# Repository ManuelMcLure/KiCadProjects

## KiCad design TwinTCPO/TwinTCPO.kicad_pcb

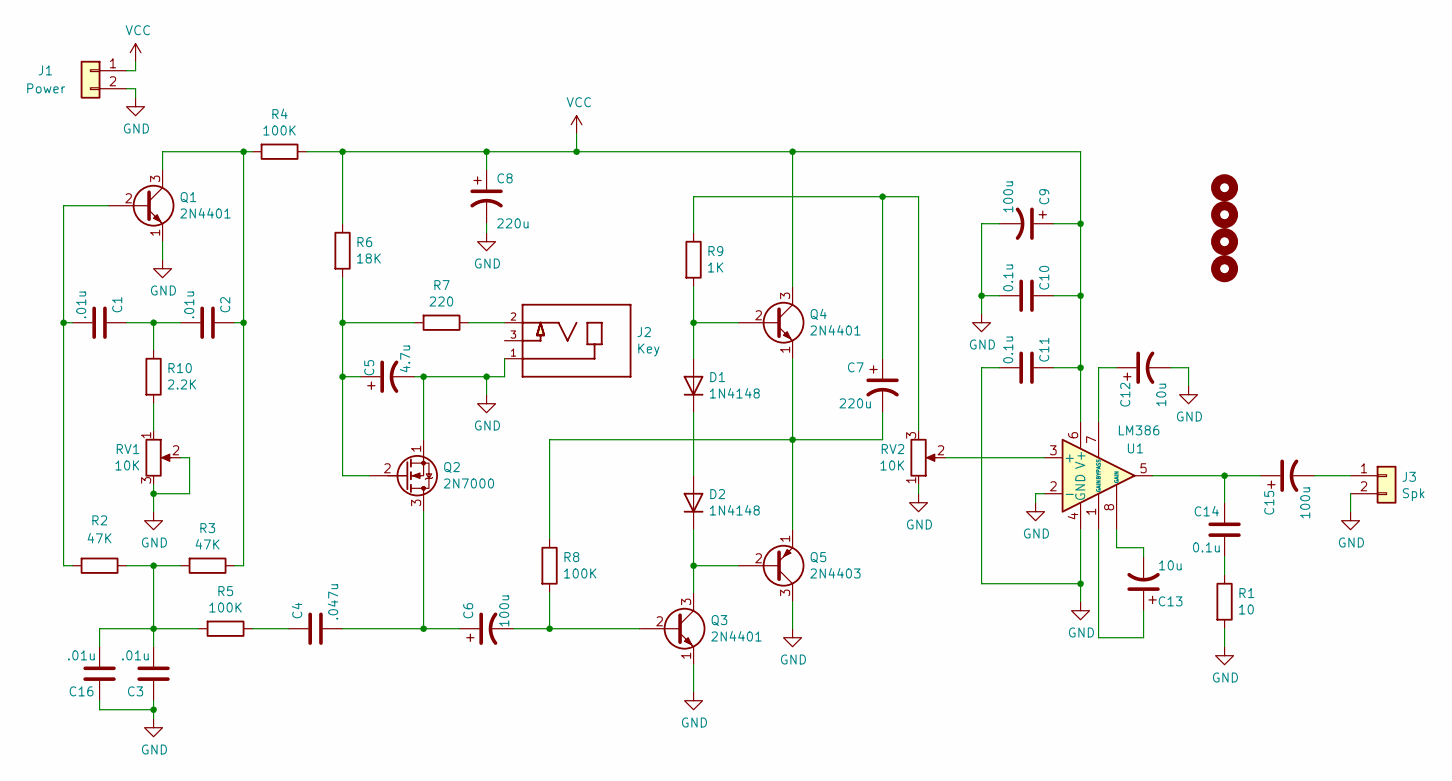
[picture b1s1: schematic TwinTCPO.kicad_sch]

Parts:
C1, C2, C3, C16: .01u; C_Disc_D4.7mm_W2.5mm_P5.00mm
C4: .047u; C_Disc_D4.7mm_W2.5mm_P5.00mm
C5: 4.7u; CP_Radial_D5.0mm_P2.50mm
C6, C9, C15: 100u; CP_Radial_D5.0mm_P2.00mm
C7, C8: 220u; CP_Radial_D6.3mm_P2.50mm
C10, C11, C14: 0.1u; C_Disc_D4.7mm_W2.5mm_P5.00mm
C12, C13: 10u; CP_Radial_D5.0mm_P2.50mm
D1, D2: 1N4148; D_DO-35_SOD27_P7.62mm_Horizontal
H1, H2, H3, H4: MountingHole; MountingHole_3.2mm_M3_DIN965
J1: Power; Molex_KK-254_AE-6410-02A_1x02_P2.54mm_Vertical
J2: Key; CUI_MJ-3536N; PART_REV B
J3: Spk; Molex_KK-254_AE-6410-02A_1x02_P2.54mm_Vertical
Q1, Q3, Q4: 2N4401; TO-92L_Inline_Wide
Q2: 2N7000; TO-92L_Inline_Wide
Q5: 2N4403; TO-92L_Inline_Wide
R1: 10; R_Axial_DIN0207_L6.3mm_D2.5mm_P2.54mm_Vertical
R2, R3: 47K; R_Axial_DIN0207_L6.3mm_D2.5mm_P2.54mm_Vertical
R4, R5, R8: 100K; R_Axial_DIN0207_L6.3mm_D2.5mm_P2.54mm_Vertical
R6: 18K; R_Axial_DIN0207_L6.3mm_D2.5mm_P2.54mm_Vertical
R7: 220; R_Axial_DIN0207_L6.3mm_D2.5mm_P2.54mm_Vertical
R9: 1K; R_Axial_DIN0207_L6.3mm_D2.5mm_P2.54mm_Vertical
R10: 2.2K; R_Axial_DIN0207_L6.3mm_D2.5mm_P2.54mm_Vertical
RV1, RV2: 10K; P120PK
U1: LM386; DIP-8_W7.62mm_Socket

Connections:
GND: C3.1, C5.2, C8.2, C9.2, C10.2, C11.2, C12.2, C16.1, J1.2, J2.1, J3.2, Q1.1 (E), Q2.1 (S), Q3.1 (E), Q5.3 (C), R1.2, RV1.2, RV1.3, RV2.1, U1.2 (-), U1.4 (GND)
unnamed: C1.1, C2.2, R10.1
unnamed: C1.2, Q1.2 (B), R2.2
unnamed: C2.1, Q1.3 (C), R3.1, R4.2
unnamed: C4.1, R5.1
unnamed: C4.2, C6.1, Q2.3 (D)
unnamed: C5.1, Q2.2 (G), R6.2, R7.2
unnamed: C6.2, Q3.2 (B), R8.2
unnamed: C7.1, R9.1, RV2.3
unnamed: C7.2, Q4.1 (E), Q5.1 (E), R8.1
unnamed: C12.1, U1.7 (BYPASS)
unnamed: C13.1, U1.1 (GAIN)
unnamed: C13.2, U1.8 (GAIN)
unnamed: C14.1, C15.1, U1.5
unnamed: C14.2, R1.1
unnamed: C15.2, J3.1
unnamed: C3.2, C16.2, R2.1, R3.2, R5.2
unnamed: D1.1 (K), D2.2 (A)
unnamed: D1.2 (A), Q4.2 (B), R9.2
unnamed: D2.1 (K), Q3.3 (C), Q5.2 (B)
unnamed: J2.2, R7.1
unnamed: R10.2, RV1.1
unnamed: RV2.2, U1.3 (+)
VCC: C8.1, C9.1, C10.1, C11.1, J1.1, Q4.3 (C), R4.1, R6.1, U1.6 (V+)

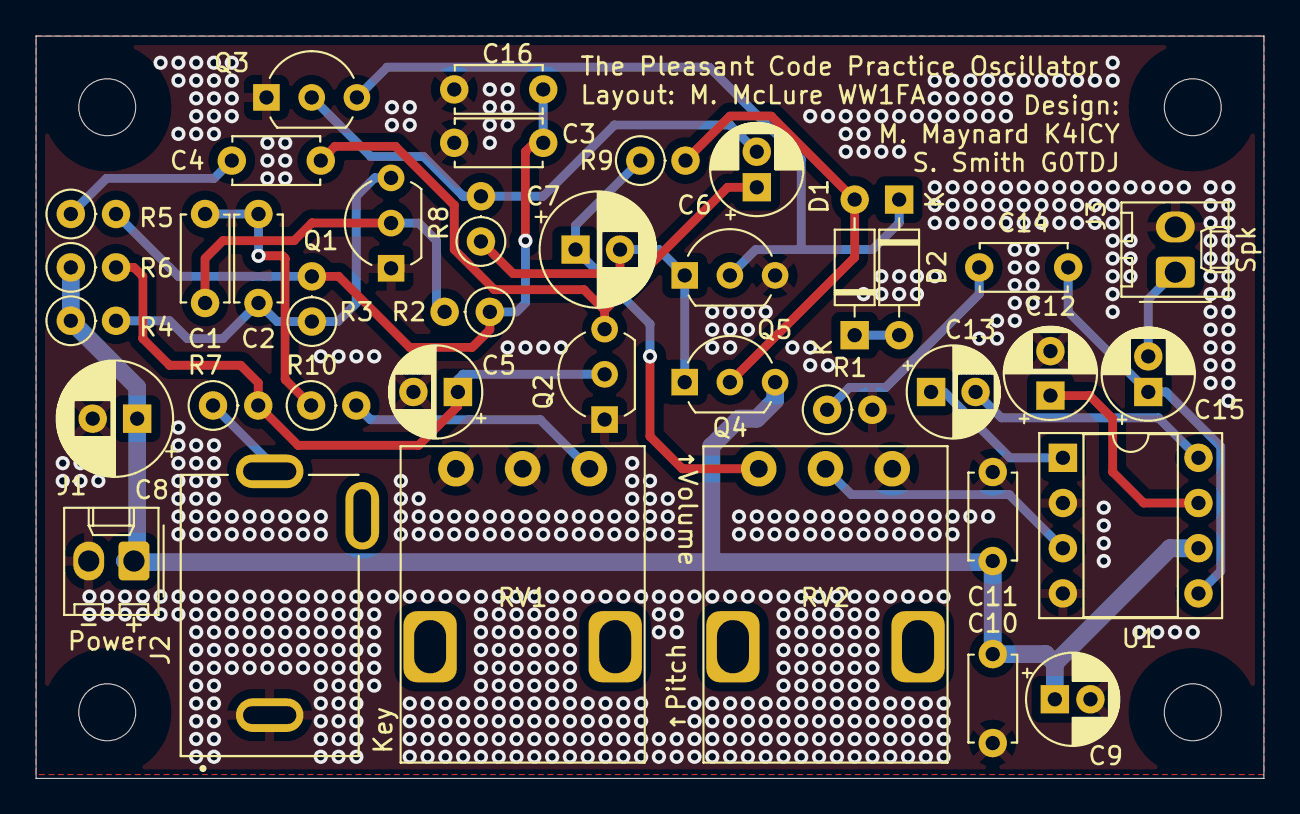
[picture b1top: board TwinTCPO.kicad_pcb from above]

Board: 2 copper layers, 69.0 x 41.7 mm, 43 parts (0 on the bottom side), 24 nets.

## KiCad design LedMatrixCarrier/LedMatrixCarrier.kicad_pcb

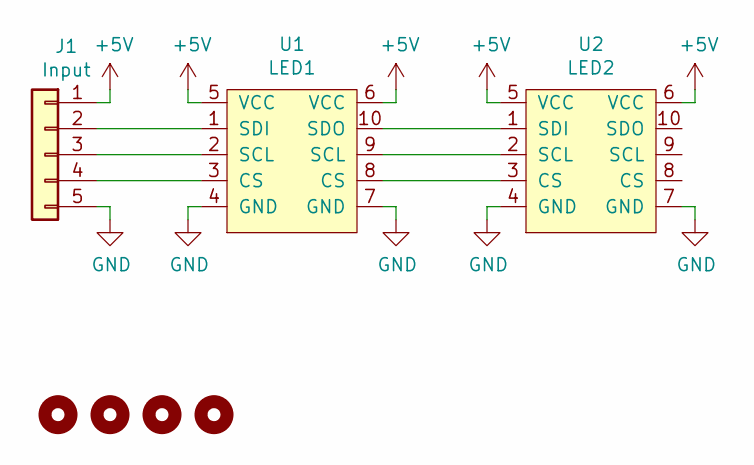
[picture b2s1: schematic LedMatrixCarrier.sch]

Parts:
H1, H2, H3, H4: MountingHole; MountingHole_3.2mm_M3_DIN965
J1: Input; PinHeader_1x05_P2.54mm_Vertical
U1: LED1; RoboDyn_MAX7221_LED_Matrix
U2: LED2; RoboDyn_MAX7221_LED_Matrix

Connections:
+5V: J1.1, U1.5 (VCC), U1.6 (VCC), U2.5 (VCC), U2.6 (VCC)
GND: J1.5, U1.4 (GND), U1.7 (GND), U2.4 (GND), U2.7 (GND)
unnamed: J1.2, U1.1 (SDI)
unnamed: J1.3, U1.2 (SCL)
unnamed: J1.4, U1.3 (CS)
unnamed: U1.8 (CS), U2.3 (CS)
unnamed: U1.9 (SCL), U2.2 (SCL)
unnamed: U1.10 (SDO), U2.1 (SDI)

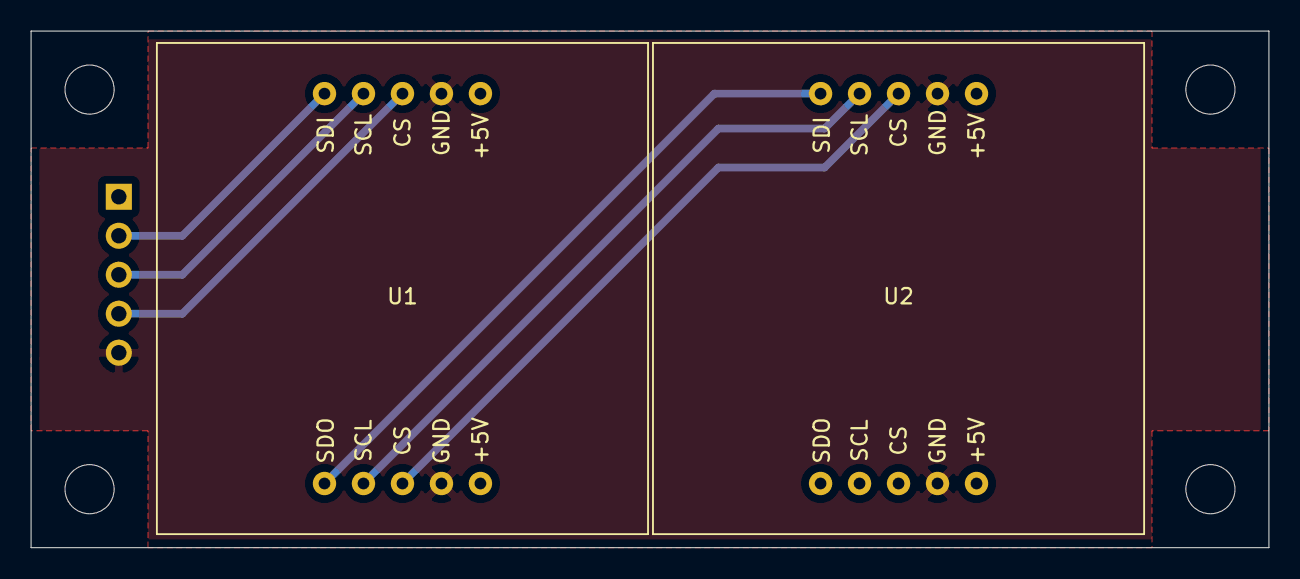
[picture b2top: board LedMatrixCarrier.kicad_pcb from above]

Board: 2 copper layers, 80.6 x 33.7 mm, 7 parts (1 on the bottom side), 8 nets.

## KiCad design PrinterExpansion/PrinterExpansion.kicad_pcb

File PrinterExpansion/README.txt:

This project requires the MyLibrary symbol and footprint libraries in ..\Libraries.

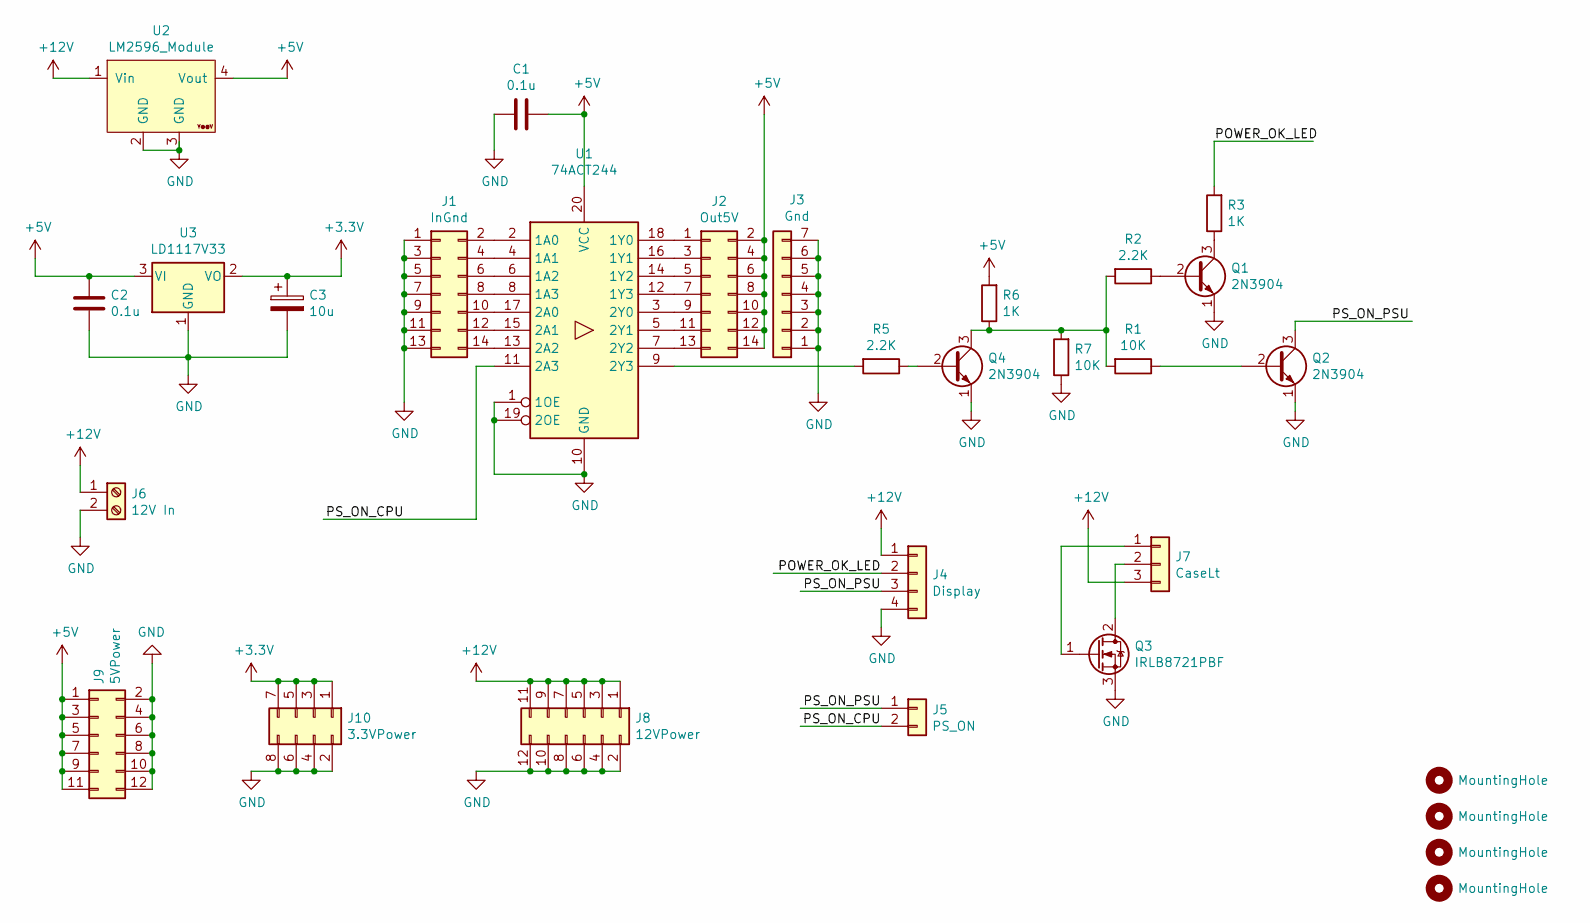
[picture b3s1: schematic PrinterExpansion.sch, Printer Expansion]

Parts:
C1, C2: 0.1u; C_Disc_D4.7mm_W2.5mm_P5.00mm
C3: 10u; CP_Radial_D5.0mm_P2.50mm
H1, H2, H3, H4: MountingHole; MountingHole_3.2mm_M3_ISO7380
J1: InGnd; PinHeader_2x07_P2.54mm_Vertical
J2: Out5V; PinHeader_2x07_P2.54mm_Vertical
J3: Gnd; PinHeader_1x07_P2.54mm_Vertical
J4: Display; Molex_KK-254_AE-6410-04A_1x04_P2.54mm_Vertical
J5: PS_ON; Molex_KK-254_AE-6410-02A_1x02_P2.54mm_Vertical
J6: 12V In; TerminalBlock_Dinkle_EK500_2Pole
J7: CaseLt; Molex_KK-254_AE-6410-03A_1x03_P2.54mm_Vertical
J8: 12VPower; PinHeader_2x06_P2.54mm_Vertical
J9: 5VPower; PinHeader_2x06_P2.54mm_Vertical
J10: 3.3VPower; PinHeader_2x04_P2.54mm_Vertical
Q1, Q2, Q4: 2N3904; TO-92_Inline_Wide
Q3: IRLB8721PBF; TO-220-3_Vertical
R1, R7: 10K; R_Axial_DIN0207_L6.3mm_D2.5mm_P10.16mm_Horizontal
R2, R5: 2.2K; R_Axial_DIN0207_L6.3mm_D2.5mm_P10.16mm_Horizontal
R3, R6: 1K; R_Axial_DIN0207_L6.3mm_D2.5mm_P10.16mm_Horizontal
U1: 74ACT244; DIP-20_W7.62mm_Socket
U2: LM2596_Module; YAAJ_DCDC_StepDown_LM2596
U3: LD1117V33; TO-220-3_Vertical

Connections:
+3V3: C3.1, J10.1, J10.3, J10.5, J10.7, U3.2 (VO)
+5V: C1.1, C2.1, J2.2, J2.4, J2.6, J2.8, J2.10, J2.12, J2.14, J9.1, J9.3, J9.5, J9.7, J9.9, J9.11, R6.2, U1.20 (VCC), U2.4 (Vout), U3.3 (VI)
+12V: J4.1, J6.1, J7.3, J8.1, J8.3, J8.5, J8.7, J8.9, J8.11, U2.1 (Vin)
/POWER_OK_LED: J4.2, R3.2
/PS_ON_CPU: J5.2, U1.11 (2A3)
/PS_ON_PSU: J4.3, J5.1, Q2.3 (C)
GND: C1.2, C2.2, C3.2, J1.1, J1.3, J1.5, J1.7, J1.9, J1.11, J1.13, J3.1, J3.2, J3.3, J3.4, J3.5, J3.6, J3.7, J4.4, J6.2, J8.2, J8.4, J8.6, J8.8, J8.10, J8.12, J9.2, J9.4, J9.6, J9.8, J9.10, J9.12, J10.2, J10.4, J10.6, J10.8, Q1.1 (E), Q2.1 (E), Q3.3 (S), Q4.1 (E), R7.1, U1.1 (1OE), U1.10 (GND), U1.19 (2OE), U2.2 (GND), U2.3 (GND), U3.1 (GND)
unnamed: J1.2, U1.2 (1A0)
unnamed: J1.4, U1.4 (1A1)
unnamed: J1.6, U1.6 (1A2)
unnamed: J1.8, U1.8 (1A3)
unnamed: J1.10, U1.17 (2A0)
unnamed: J1.12, U1.15 (2A1)
unnamed: J1.14, U1.13 (2A2)
unnamed: J2.1, U1.18 (1Y0)
unnamed: J2.3, U1.16 (1Y1)
unnamed: J2.5, U1.14 (1Y2)
unnamed: J2.7, U1.12 (1Y3)
unnamed: J2.9, U1.3 (2Y0)
unnamed: J2.11, U1.5 (2Y1)
unnamed: J2.13, U1.7 (2Y2)
unnamed: J7.1, Q3.1 (G)
unnamed: J7.2, Q3.2 (D)
unnamed: Q1.2 (B), R2.1
unnamed: Q1.3 (C), R3.1
unnamed: Q2.2 (B), R1.1
unnamed: Q4.2 (B), R5.1
unnamed: Q4.3 (C), R1.2, R2.2, R6.1, R7.2
unnamed: R5.2, U1.9 (2Y3)

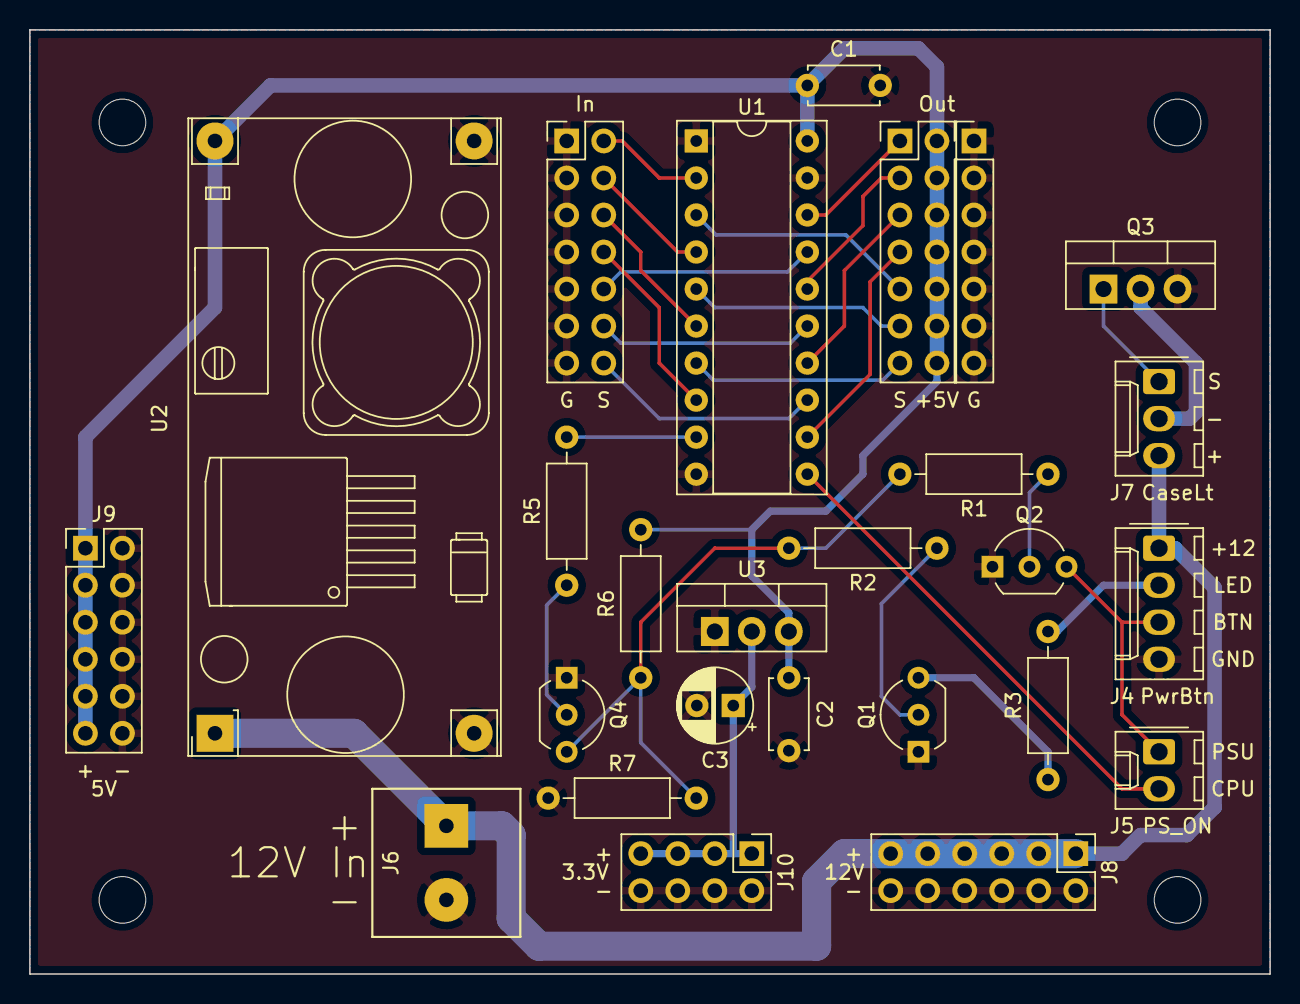
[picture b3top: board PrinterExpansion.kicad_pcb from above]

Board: 2 copper layers, 85.1 x 64.8 mm, 30 parts (0 on the bottom side), 29 nets.

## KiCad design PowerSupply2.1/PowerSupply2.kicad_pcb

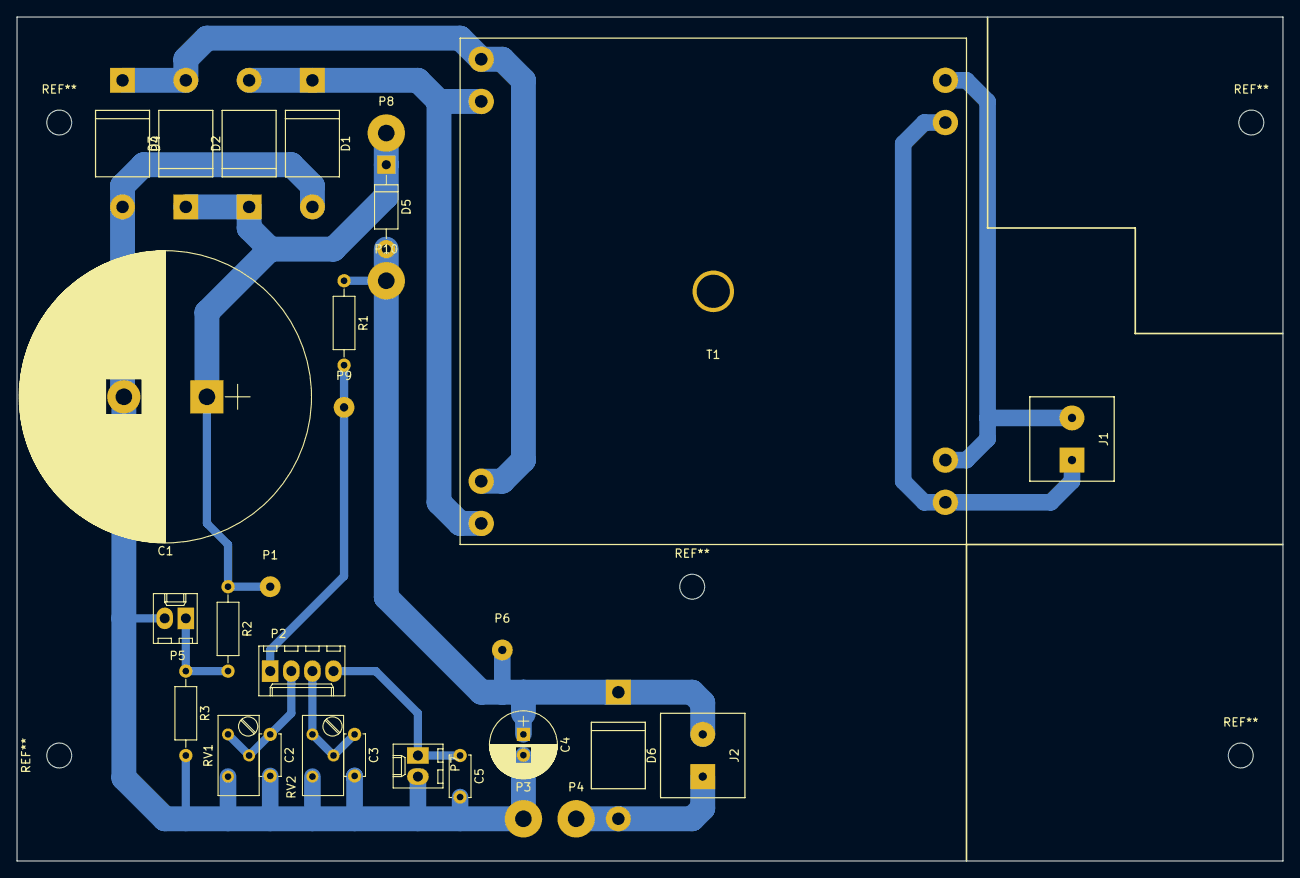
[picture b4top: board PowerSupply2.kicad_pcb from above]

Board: 2 copper layers, 152.4 x 101.6 mm, 29 parts (0 on the bottom side), 13 nets.

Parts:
C1: 27000uF 25V; CP_Radial_D35.0mm_P10.00mm_SnapIn
C2, C3, C5: 10uF; C_Disc_D5.0mm_W2.5mm_P5.00mm
C4: 150uF; CP_Radial_D8.0mm_P2.50mm
D1, D2, D3, D4, D6: RK46
D5: 1N4001; D_DO-41_SOD81_P10.16mm_Horizontal
J1: AC_In; TerminalBlock_Dinkle_EK500_2Pole
J2: VOut; TerminalBlock_Dinkle_EK500_2Pole
P1: DispPwr; SolderWirePad_single_1mmDrill
P2: VSelect; Molex_KK-6410-04_04x2.54mm_Straight
P3: Curr-; SolderWirePad_single_2mmDrill
P4: Curr+; SolderWirePad_single_2mmDrill
P5: PWR_LED; Molex_KK-6410-02_02x2.54mm_Straight
P6: VSense; SolderWirePad_single_1mmDrill
P7: VVar; Molex_KK-6410-02_02x2.54mm_Straight
P8: VRegIn; SolderWirePad_single_2mmDrill
P9: VRegAdj; SolderWirePad_single_1mmDrill
P10: VRegOut; SolderWirePad_single_2mmDrill
R1: 121; R_Axial_DIN0207_L6.3mm_D2.5mm_P10.16mm_Horizontal
R2: 150; R_Axial_DIN0207_L6.3mm_D2.5mm_P10.16mm_Horizontal
R3: 1K; R_Axial_DIN0207_L6.3mm_D2.5mm_P10.16mm_Horizontal
RV1, RV2: 500; Potentiometer_Trimmer_Bourns_3296Y
T1: Talema_70060K

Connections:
/AC7V_1: D1.1, D2.2, T1.11, T1.13
/AC7V_2: D3.2, D4.1, T1.12, T1.14
/ACLive: J1.1, T1.4, T1.6
/ACNeutral: J1.2, T1.3, T1.5
/Gnd: C1.2, C2.2, C3.2, C4.2, C5.2, D1.2, D4.2, P3.1, P5.2, P7.2, R3.2, RV1.3, RV2.3
/Reg+: C4.1, D5.2, D6.1, J2.2, P6.1, P10.1, R1.1
/Unreg+: C1.1, D2.1, D3.1, D5.1, P1.1, P8.1, R2.1
unnamed: C2.1, P2.2, RV1.1, RV1.2
unnamed: C3.1, P2.3, RV2.1, RV2.2
unnamed: C5.1, P2.4, P7.1
unnamed: D6.2, J2.1, P4.1
unnamed: P2.1, P9.1, R1.2
unnamed: P5.1, R2.2, R3.1

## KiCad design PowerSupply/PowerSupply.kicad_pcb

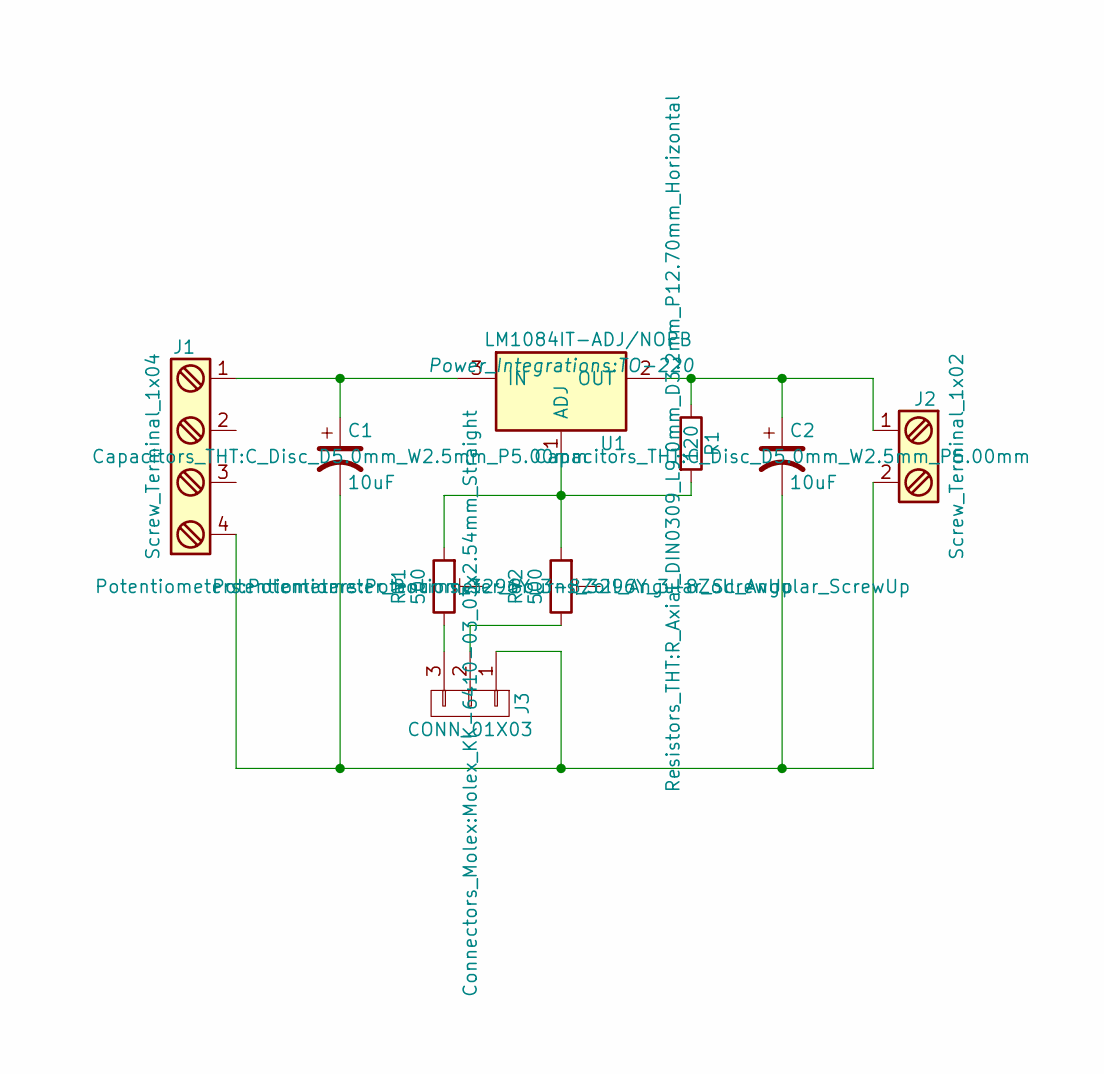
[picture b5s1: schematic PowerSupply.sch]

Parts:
C1, C2: 10uF; C_Disc_D5.0mm_W2.5mm_P5.00mm
J1: Screw_Terminal_1x04; TerminalBlock_Pheonix_MKDS1.5-4pol
J2: Screw_Terminal_1x02; TerminalBlock_Pheonix_MKDS1.5-2pol
J3: CONN_01X03; Molex_KK-6410-03_03x2.54mm_Straight
R1: 120; R_Axial_DIN0309_L9.0mm_D3.2mm_P12.70mm_Horizontal
RV1, RV2: 500; Potentiometer_Bourns_3296Y_3-8Zoll_Angular_ScrewUp
U1: LM1084IT-ADJ/NOPB; TO-220

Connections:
unnamed: C1.1, J1.1, U1.3 (IN)
unnamed: C1.2, C2.2, J1.4, J2.2, J3.1
unnamed: C2.1, J2.1, R1.1, U1.2 (OUT)
unnamed: J3.2, RV2.3
unnamed: J3.3, RV1.3
unnamed: R1.2, RV1.1, RV2.1, U1.1 (ADJ)

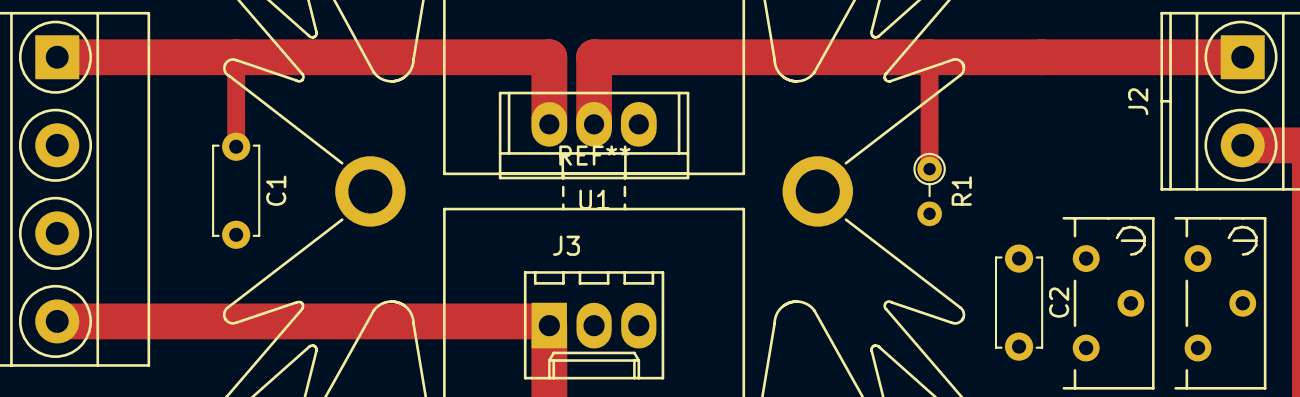
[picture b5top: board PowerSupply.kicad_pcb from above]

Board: 2 copper layers, 9 parts (0 on the bottom side), 6 nets.

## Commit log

2021-09-18 Initial checkin
2021-09-18 Change license and add text to PCB.
2021-09-18 Use actual copyright symbol
2021-09-18 Fix buck module 3D view.
2021-09-19 Fix library references
2021-09-20 Fix library references (again)
2021-10-10 Fix origin
2021-10-13 Add RoboDyn MAX7221 LED Matrix
2021-10-13 Check in LED Matrix carrier
2021-10-14 Add Gerbers to ignored files
2021-10-17 First checking TwinTCPO
2021-10-22 P129PK pot footprint
2021-10-23 Add new components
2021-10-23 Ready for production
2021-10-23 Fix for Kicad 5.99/6.x
2021-10-23 Bring up to Kicad 5.99/6.x
2021-10-25 Fix mounting hole clearance.
2021-10-26 Sync schematic and PCB
2021-11-27 Change resistors for lower frequency
2021-11-28 Start at version 2
    * Remove headphone jack
    * Change R2/R3 for lower frequency
    * Add 2.2K resistor in series with RV1
2021-12-12 V2.0 final

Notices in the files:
PrinterExpansion/PrinterExpansion.kicad_pcb:
©2021 Manuel McLure
Licensed under Creative Commons
Attribution-ShareAlike 4.0 International
